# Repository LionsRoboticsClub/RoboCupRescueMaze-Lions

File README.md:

# RoboCupRescueMaze-Lions DONE TMR 201X
RoboCup Rescue Maze 

//CAD Render 2 months before final prototype -> https://autode.sk/2EDeenq

TODO ---- Add new Online Render 

This Repository holds all the data regarding the Lions RC Maze Robot - 2018.

Some of the content that can be found here is: 

PCBs
  Eagle files
  Gerber files
Arduino Code
  Classes
  Main
CADs
  Each piece is uploaded here for further reference and 3D printing

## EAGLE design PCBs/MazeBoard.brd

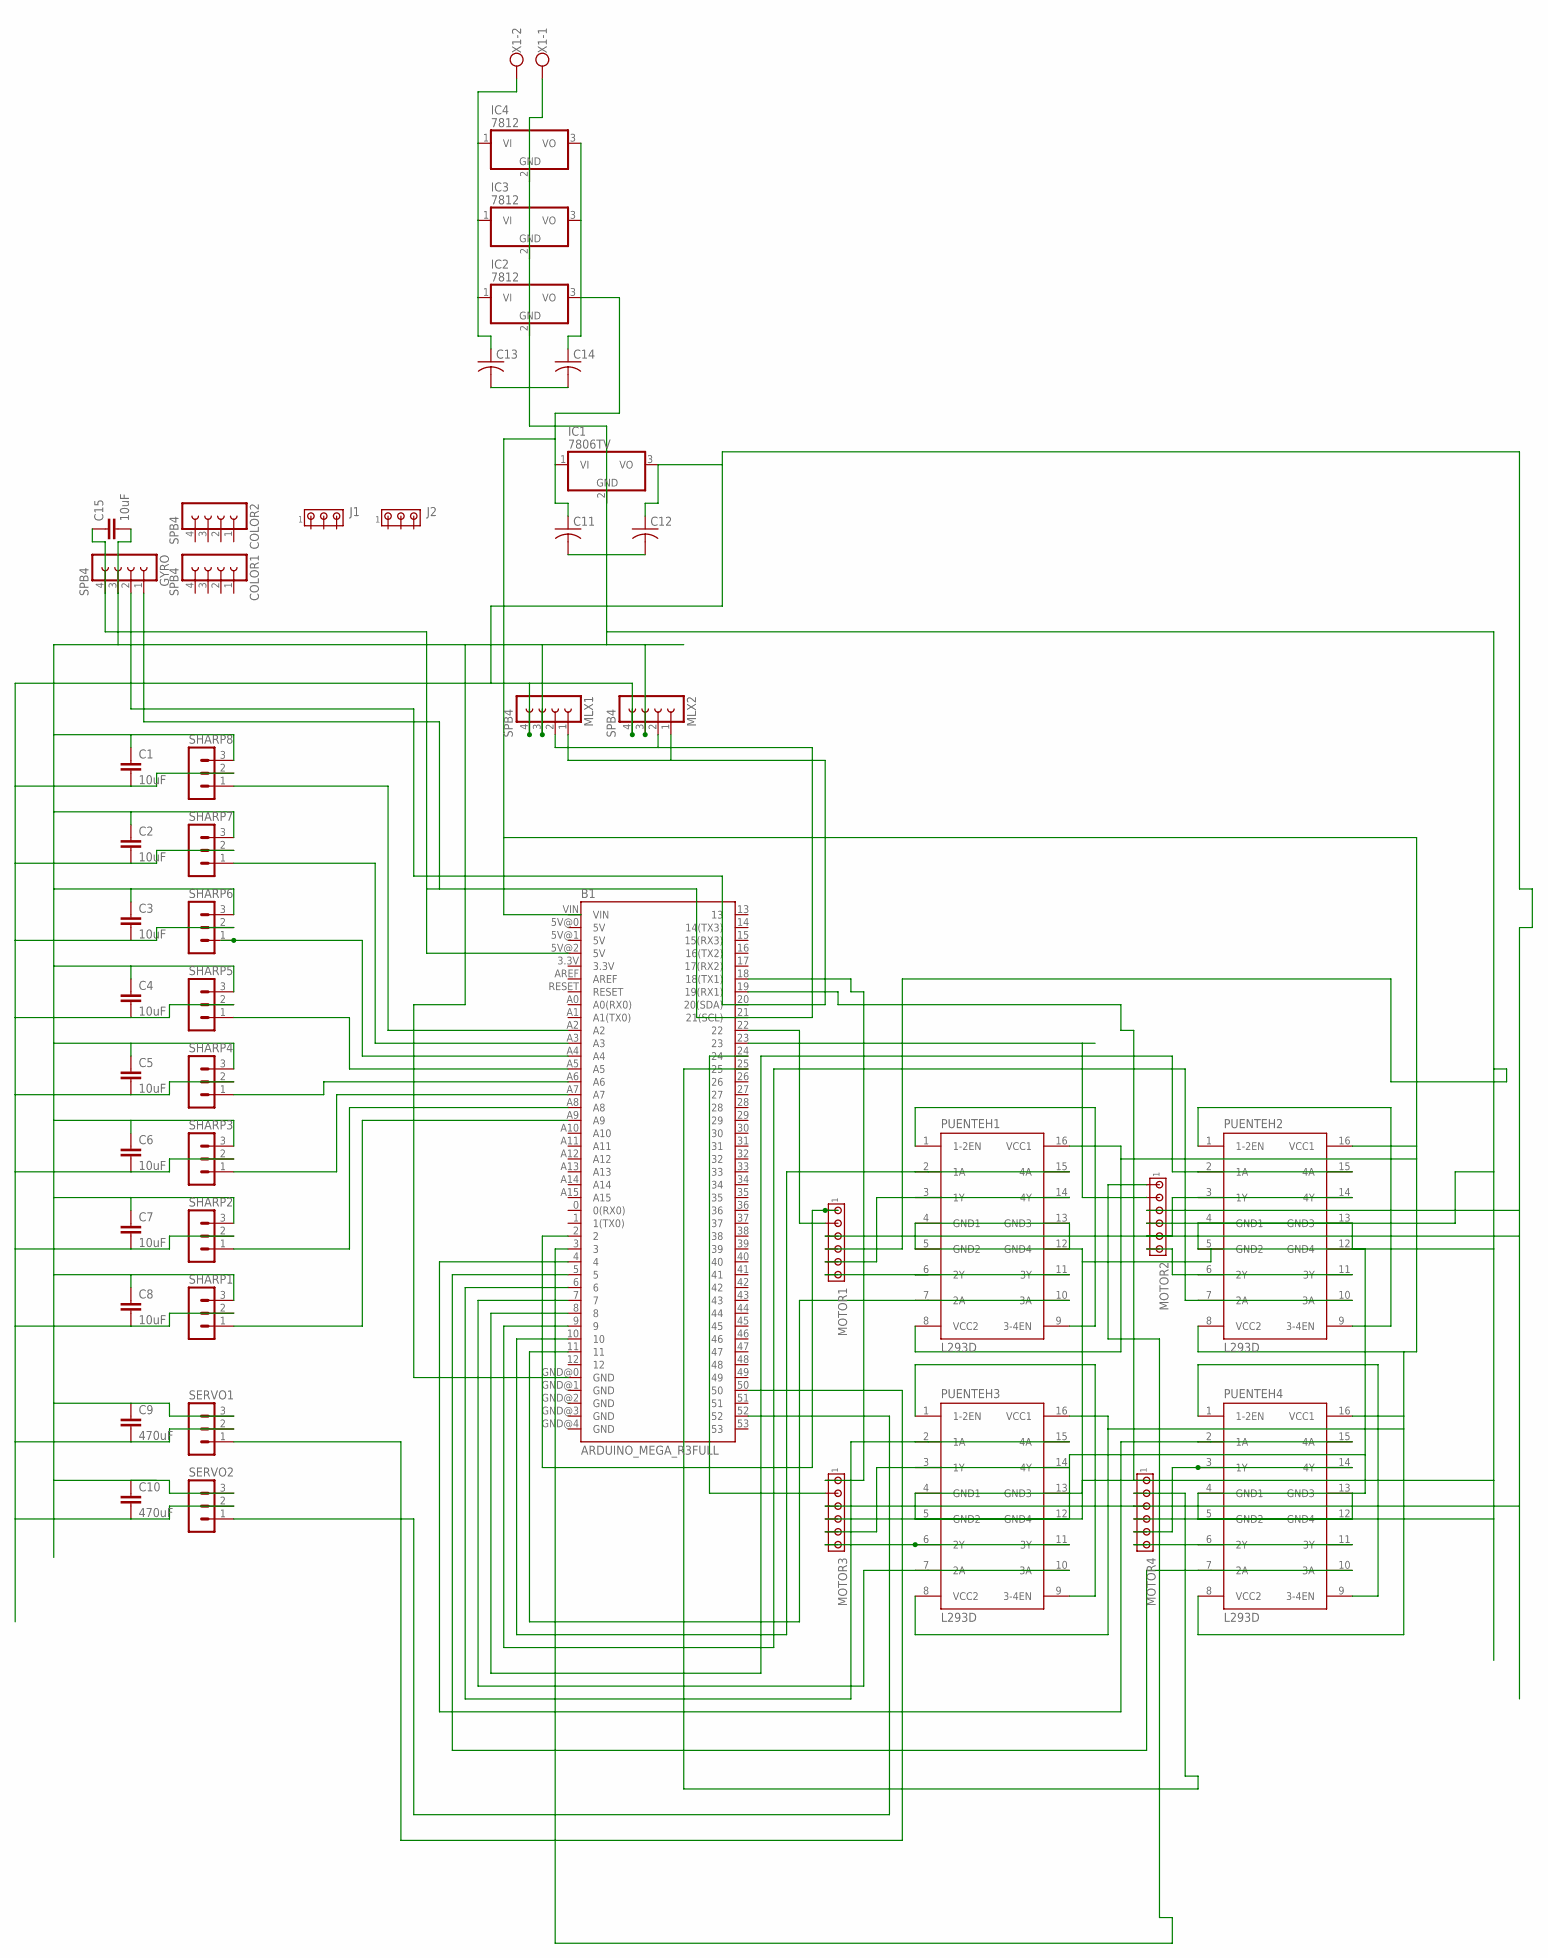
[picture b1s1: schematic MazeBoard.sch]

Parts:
B1: ARDUINO_MEGA_R3FULL; ARDUINO_MEGA
C1, C2, C3, C4, C5, C6, C7, C8, C15: 10uF; C2.5-3
C9, C10: 470uF; C2.5-3
C11, C12, C13, C14: C-US025-024X044; C025-024X044
COLOR1, COLOR2: SPB4
GYRO: SPB4
IC1: 7806TV; TO220V
IC2, IC3, IC4: 7812; TO220V
J1, J2: MTA03-100; 10X03MTA
MLX1, MLX2: SPB4
MOTOR1, MOTOR2, MOTOR3, MOTOR4: MTA06-100; 10X06MTA
PUENTEH1, PUENTEH2, PUENTEH3, PUENTEH4: L293D; DIL16
SERVO1, SERVO2: MA03-1
SHARP1, SHARP2, SHARP3, SHARP4, SHARP5, SHARP6, SHARP7, SHARP8: MA03-1
X1: W237-102

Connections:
6V: C1.2, C2.2, C3.2, C4.2, C5.2, C6.2, C7.2, C8.2, C9.2, C10.2, C12.1, IC1.3 (VO), MLX1.4, MLX2.4, MOTOR1.3, MOTOR2.3, MOTOR3.3, MOTOR4.3, SERVO1.2, SERVO2.2, SHARP1.2, SHARP2.2, SHARP3.2, SHARP4.2, SHARP5.2, SHARP6.2, SHARP7.2, SHARP8.2
GND: B1.GND@0 (GND), C1.1, C2.1, C3.1, C4.1, C5.1, C6.1, C7.1, C8.1, C9.1, C10.1, C11.2, C12.2, C13.2, C14.2, C15.2, GYRO.3, IC1.2 (GND), IC2.2 (GND), IC3.2 (GND), IC4.2 (GND), MLX1.3, MLX2.3, MOTOR1.4, MOTOR2.4, MOTOR3.4, MOTOR4.4, PUENTEH1.4 (GND1), PUENTEH1.5 (GND2), PUENTEH1.12 (GND4), PUENTEH1.13 (GND3), PUENTEH2.4 (GND1), PUENTEH2.5 (GND2), PUENTEH2.12 (GND4), PUENTEH2.13 (GND3), PUENTEH3.4 (GND1), PUENTEH3.5 (GND2), PUENTEH3.12 (GND4), PUENTEH3.13 (GND3), PUENTEH4.4 (GND1), PUENTEH4.5 (GND2), PUENTEH4.12 (GND4), PUENTEH4.13 (GND3), SERVO1.3, SERVO2.3, SHARP1.3, SHARP2.3, SHARP3.3, SHARP4.3, SHARP5.3, SHARP6.3, SHARP7.3, SHARP8.3, X1.1
unnamed: B1.A4, SHARP6.1
unnamed: B1.A5, SHARP5.1
unnamed: B1.A6, SHARP4.1
unnamed: B1.A7, SHARP3.1
unnamed: B1.A2, SHARP8.1
unnamed: B1.A3, SHARP7.1
unnamed: B1.A8, SHARP2.1
unnamed: B1.A9, SHARP1.1
unnamed: B1.52, SERVO2.1
unnamed: B1.3, MOTOR2.1
unnamed: B1.21 (21(SCL)), GYRO.1, MLX1.2, MLX2.2
unnamed: B1.20 (20(SDA)), GYRO.2, MLX1.1, MLX2.1
unnamed: B1.5V@2 (5V), C15.1, GYRO.4
unnamed: PUENTEH1.1 (1-2EN), PUENTEH1.9 (3-4EN)
unnamed: MOTOR3.6, PUENTEH3.6 (2Y), PUENTEH3.11 (3Y)
unnamed: MOTOR3.5, PUENTEH3.3 (1Y), PUENTEH3.14 (4Y)
unnamed: MOTOR4.6, PUENTEH4.6 (2Y), PUENTEH4.11 (3Y)
unnamed: MOTOR4.5, PUENTEH4.3 (1Y), PUENTEH4.14 (4Y)
unnamed: MOTOR1.6, PUENTEH1.6 (2Y), PUENTEH1.11 (3Y)
unnamed: MOTOR1.5, PUENTEH1.3 (1Y), PUENTEH1.14 (4Y)
unnamed: MOTOR2.5, PUENTEH2.3 (1Y), PUENTEH2.14 (4Y)
unnamed: MOTOR2.6, PUENTEH2.6 (2Y), PUENTEH2.11 (3Y)
unnamed: PUENTEH3.1 (1-2EN), PUENTEH3.9 (3-4EN)
unnamed: PUENTEH4.1 (1-2EN), PUENTEH4.9 (3-4EN)
unnamed: B1.7, PUENTEH3.7 (2A), PUENTEH3.10 (3A)
unnamed: B1.6, PUENTEH3.2 (1A), PUENTEH3.15 (4A)
unnamed: B1.4, PUENTEH4.2 (1A), PUENTEH4.15 (4A)
unnamed: B1.5, PUENTEH4.7 (2A), PUENTEH4.10 (3A)
unnamed: B1.11, PUENTEH1.7 (2A), PUENTEH1.10 (3A)
unnamed: B1.10, PUENTEH1.2 (1A), PUENTEH1.15 (4A)
unnamed: B1.2, MOTOR1.1
unnamed: B1.9, PUENTEH2.7 (2A), PUENTEH2.10 (3A)
unnamed: PUENTEH2.1 (1-2EN), PUENTEH2.9 (3-4EN)
unnamed: B1.18 (18(TX1)), MOTOR3.1
unnamed: B1.19 (19(RX1)), MOTOR4.1
unnamed: B1.50, SERVO1.1
unnamed: B1.22, MOTOR1.2
unnamed: B1.8, PUENTEH2.2 (1A), PUENTEH2.15 (4A)
unnamed: B1.24, MOTOR3.2
unnamed: B1.25, MOTOR4.2
unnamed: B1.23, MOTOR2.2
unnamed: C11.1, C14.1, IC1.1 (VI), IC2.3 (VO), IC3.3 (VO), IC4.3 (VO), PUENTEH1.8 (VCC2), PUENTEH1.16 (VCC1), PUENTEH2.8 (VCC2), PUENTEH2.16 (VCC1), PUENTEH3.8 (VCC2), PUENTEH3.16 (VCC1), PUENTEH4.8 (VCC2), PUENTEH4.16 (VCC1)
unnamed: C13.1, IC2.1 (VI), IC3.1 (VI), IC4.1 (VI), X1.2

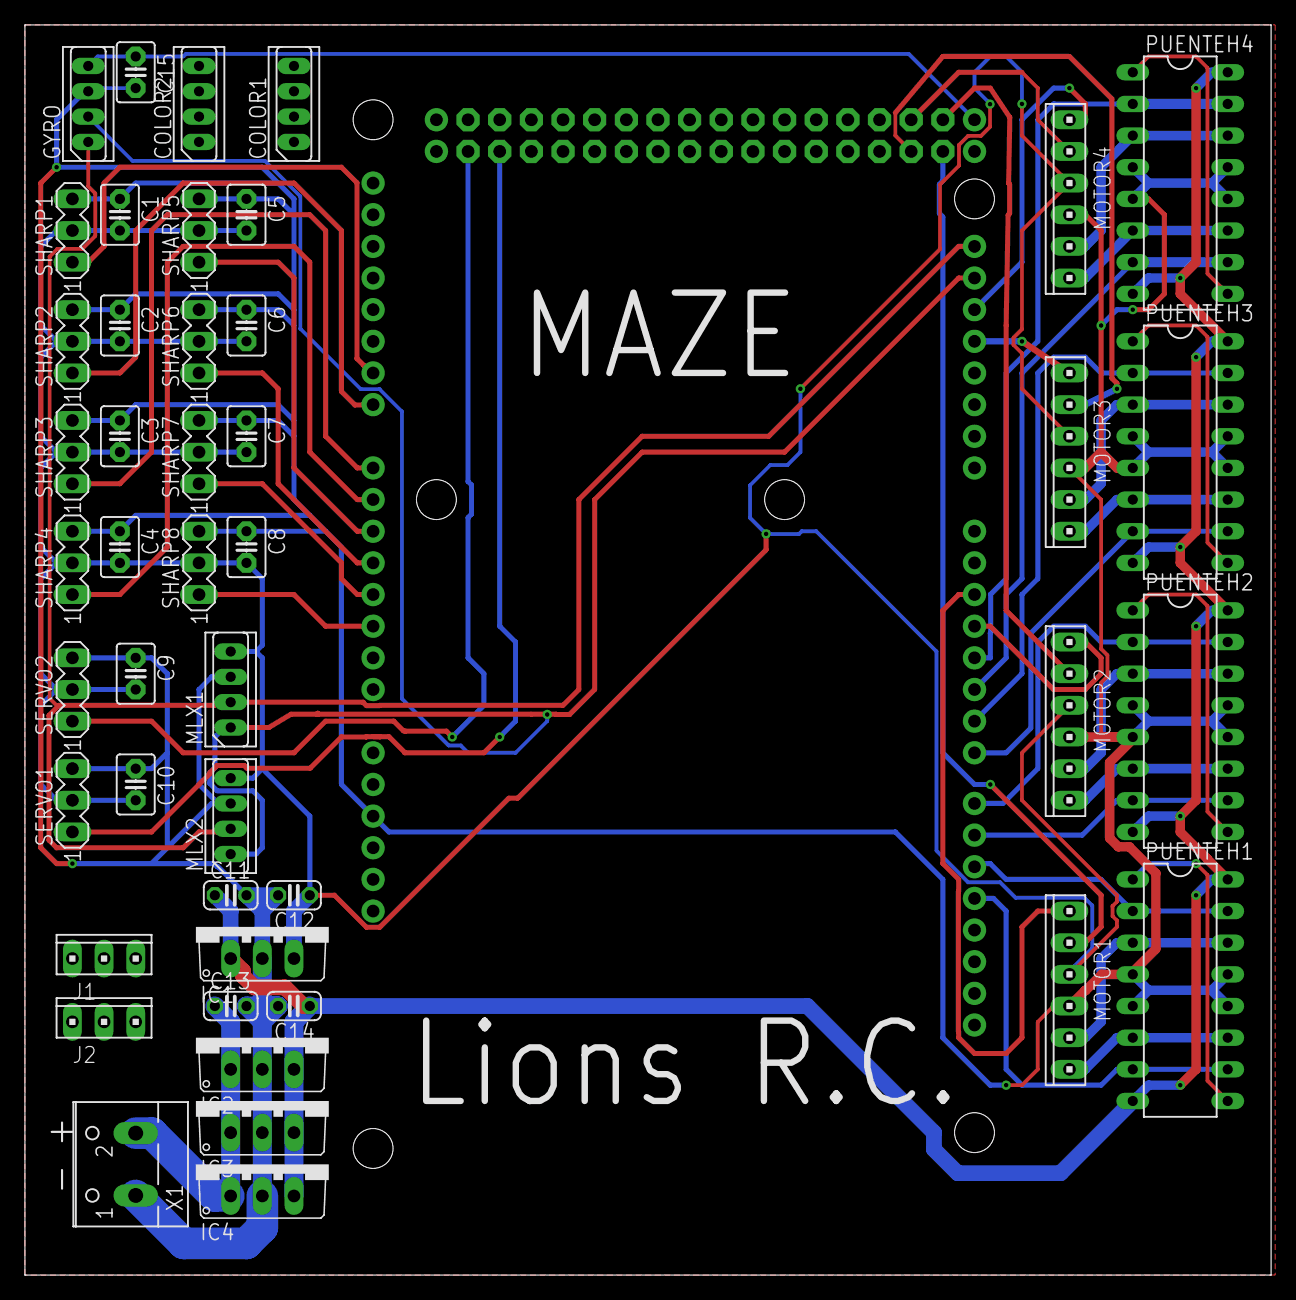
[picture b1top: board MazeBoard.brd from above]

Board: 2 copper layers, 100.0 x 100.3 mm, 46 parts (1 on the bottom side), 45 nets.

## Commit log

2017-12-21 Add files via upload
    80%
2018-03-09 Added robot code
2018-03-09 Added rotation and forward functions to Code
2018-03-10 Added Sensors classes
2018-03-10 Added intensity as a parameter to some methods
    backward(int intensity)
    forward(int intensity)
    created turnLeft and turnRight with intensity as a parameter
2018-03-10 Added Melexis library
2018-03-10 Added Class Thermometer
    Compiled but not tested
2018-03-10 Added Class LimitSwitch
2018-03-10 Added rotation by encoders
2018-03-11 Added forward by 30 cm
2018-03-12 Added classes Navigation, Tile, and Wall
2018-03-12 Added class Control and restructured other clases
2018-03-13 Added class control, and reestructured move functions
2018-03-14 Added navigation methods
2018-03-15 Fixed navigation bugs
2018-03-15 Fixed side scanning algorithm
2018-03-16 Added Nextion libraries
    Added Nextion libraries
2018-03-17 Added align methods to control class
2018-03-17 Added node search algorithm
2018-03-18 Added node search implementation
2018-03-18 Added SoftwareSerial
2018-03-18 Added debugging with Nextion
2018-03-18 Added Nextion class
2018-03-18 Debugged node tracing
2018-03-18 Debugged Node search and tracing, working
2018-03-18 Added erase Nodes function
2018-03-19 Added maze complete instructions
2018-03-19 Debugged tracing
2018-03-19 Finished navigation code
2018-03-20 Added sensors scanning and aligning
2018-03-20 Added color identification
2018-03-20 Added color sensor
2018-03-21 Added ramp support, still in progress
2018-03-21 Added maze change functionality
2018-03-22 Fixed color sensor bug
2018-03-22 Added checkpoint button functionality
2018-12-19 New link for the same CAD
2019-03-19 ROBOT DONE, CODING DONE . FINAL TESTS
2019-03-21 after match graphical map file generation added
2019-03-22 NEW ROBOT DEPLOYMENT

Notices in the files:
parts and their libraries:
SparkFun-Boards: Licensing: Creative Commons ShareAlike 4.0 International - https://creativecommons.org/licenses/by-sa/4.0
